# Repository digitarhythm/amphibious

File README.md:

# Amphibious
TReK Amphibious KiCAD Project

[Firmware repository](https://github.com/digitarhythm/vial-qmk/tree/digitarhythm/keyboards/trek/amphibious)

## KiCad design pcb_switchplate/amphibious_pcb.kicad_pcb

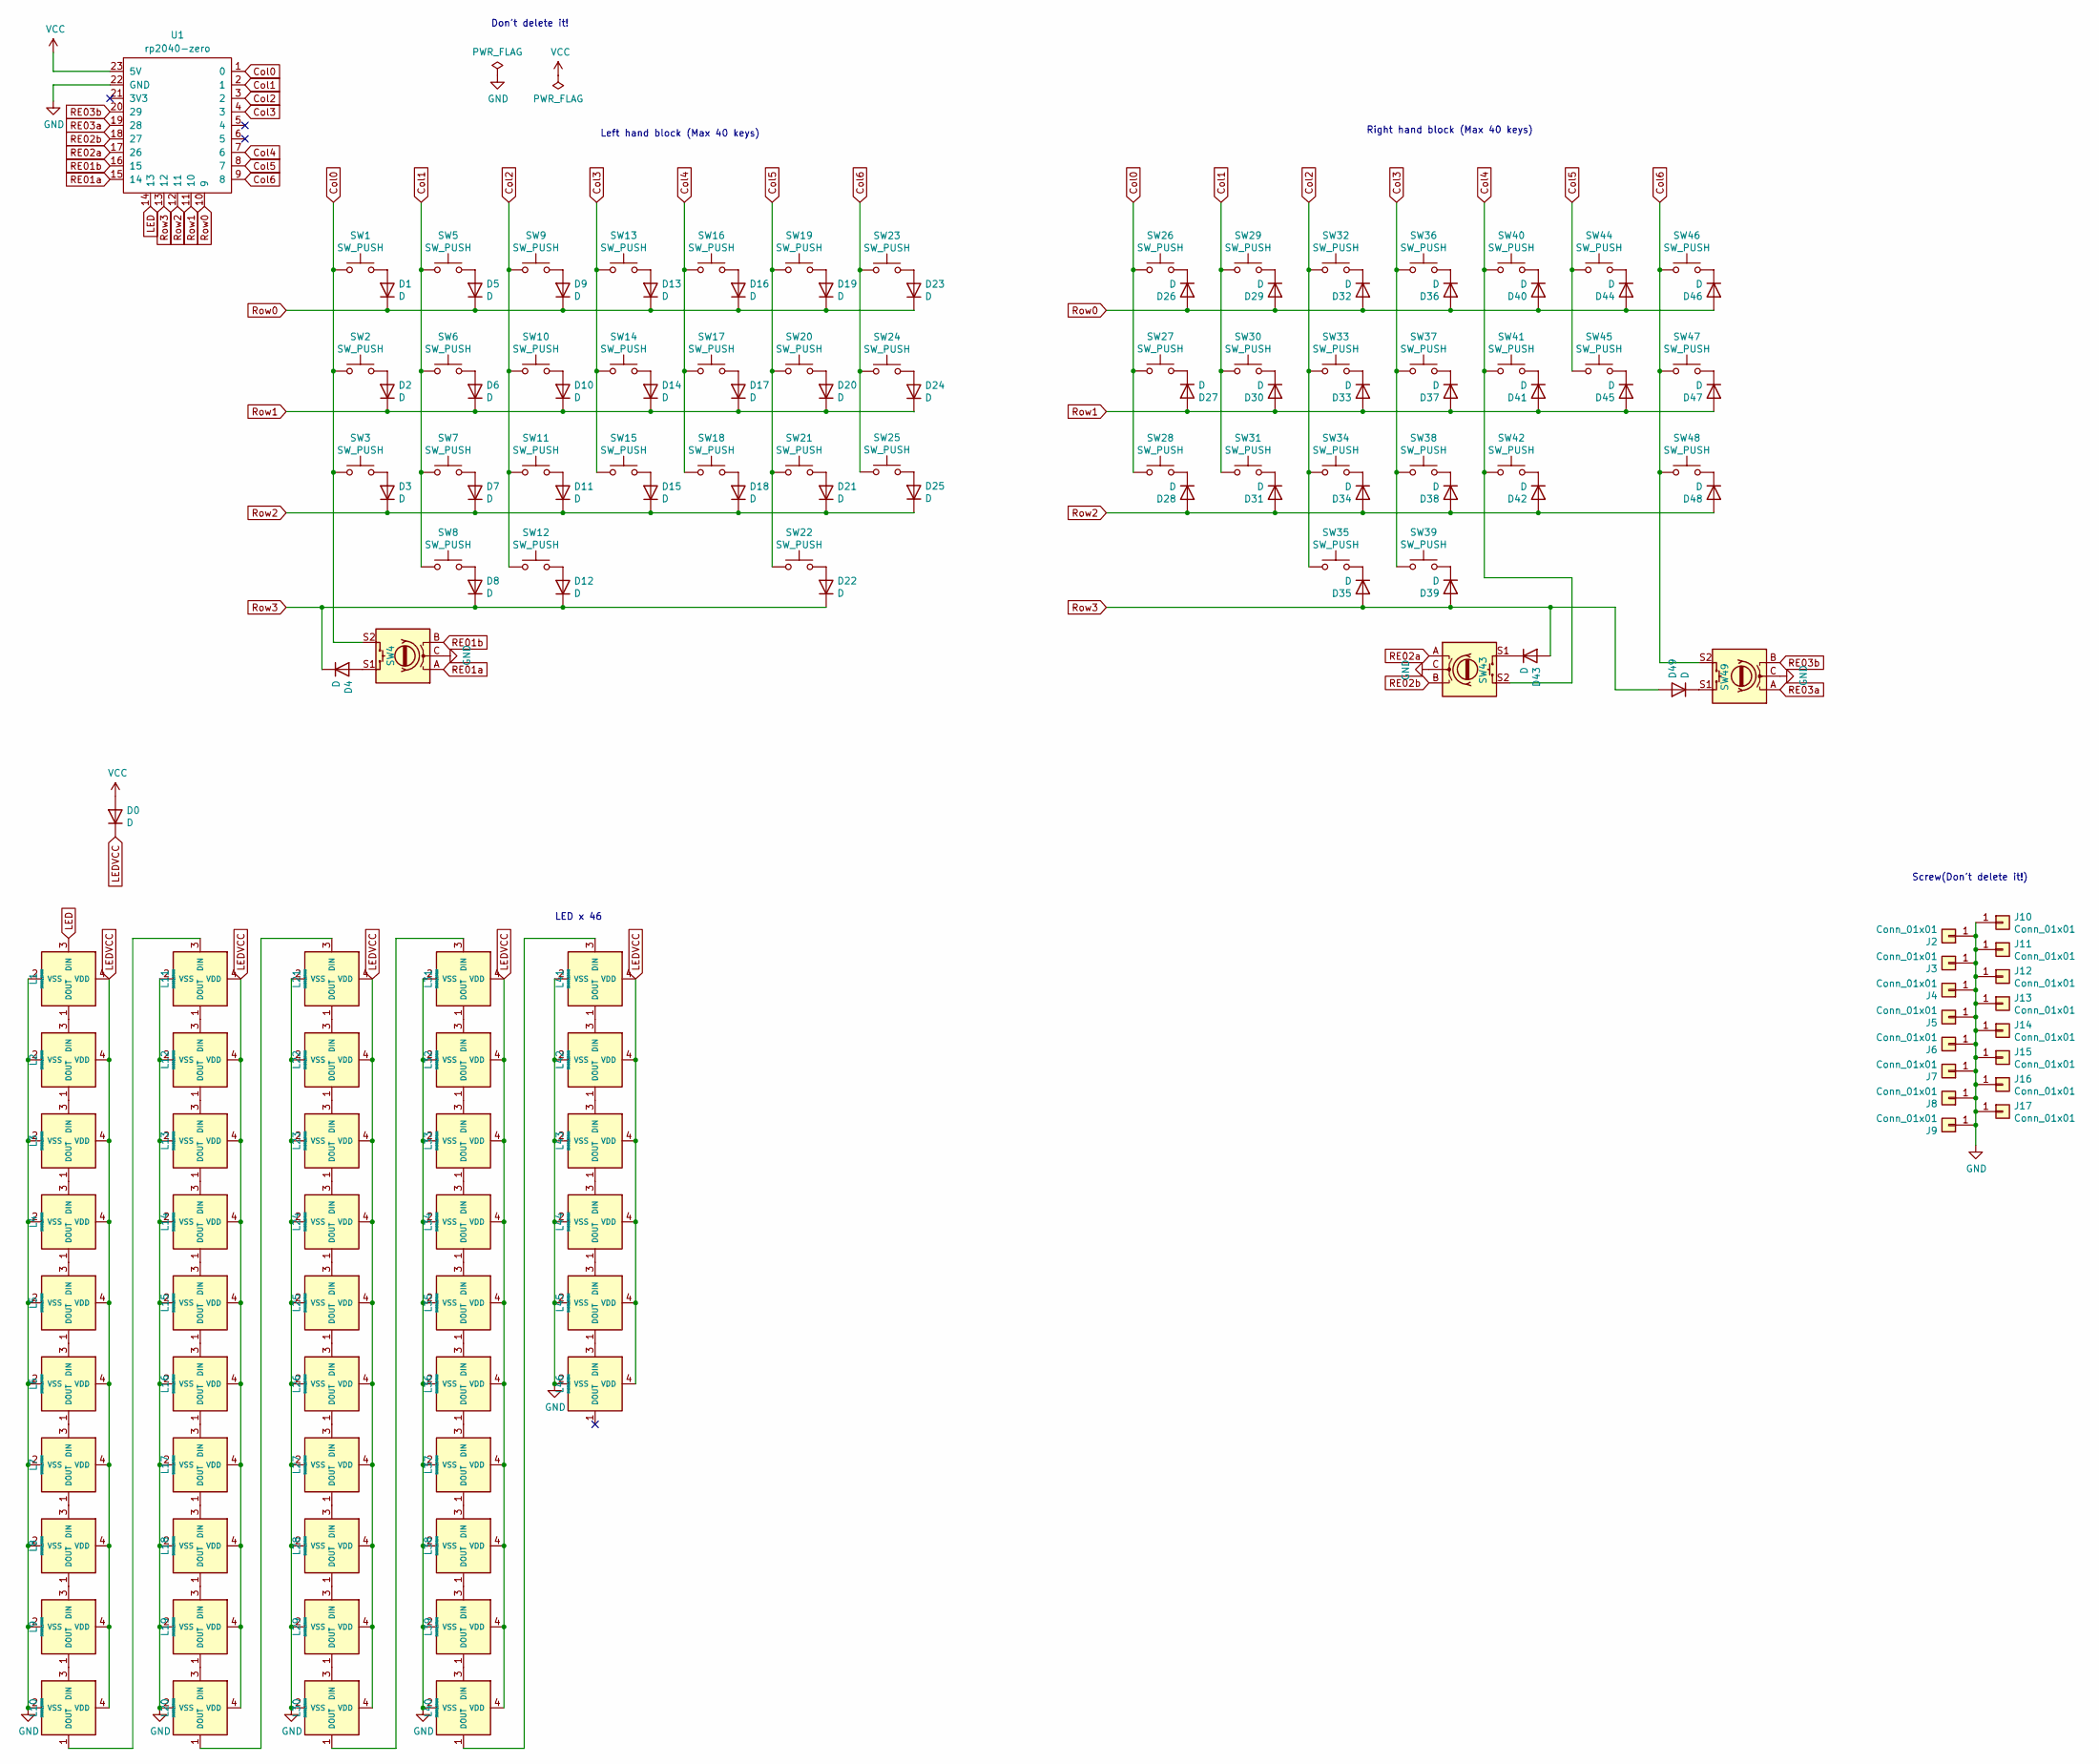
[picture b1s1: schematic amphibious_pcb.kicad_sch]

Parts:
D0, D1, D2, D3, D4, D5, D6, D7, D8, D9, D10, D11, D12, D13, D14, D15, D16, D17, D18, D19, D20, D21, D22, D23, D24, D25, D26, D27, D28, D29, D30, D31, D32, D33, D34, D35, D36, D37, D38, D39, D40, D41, D42, D43, D44, D45, D46, D47, D48, D49: D; Diode_SMD
J2, J3, J4, J5, J6, J7: Conn_01x01; m2_Spacer_Hole_EdgeCuts
J8, J9, J10, J11, J12, J13, J14, J15, J16, J17: Conn_01x01; m2_Screw_Hole_Fab
L1, L2, L3, L4, L5, L6, L7, L8, L9, L10, L11, L12, L13, L14, L15, L16, L17, L18, L19, L20, L21, L22, L23, L24, L25, L26, L27, L28, L29, L30, L31, L32, L33, L34, L35, L36, L37, L38, L39, L40, L41, L42, L43, L44, L45, L46: SK6812MINI; LED_SK6812MINI-E_BL
SW1, SW5, SW6, SW7, SW8, SW9, SW10, SW11, SW13, SW14, SW15, SW16, SW17, SW18, SW19, SW20, SW21, SW23, SW24, SW25, SW26, SW27, SW28, SW29, SW30, SW31, SW32, SW33, SW34, SW36, SW37, SW38, SW40, SW41, SW42, SW44, SW45: SW_PUSH; CherryMX_Hotswap_1u
SW2, SW12, SW35, SW39, SW47: SW_PUSH; CherryMX_Hotswap_1.25u
SW3, SW48: SW_PUSH; CherryMX_Hotswap_1.75u
SW4, SW43, SW49: RotaryEncoder_Switch; SW_Cherry_MX_1.00u_Kailh_EC12
SW22: SW_PUSH; CherryMX_Hotswap_6.25u
SW46: SW_PUSH; CherryMX_Hotswap_1.5u
U1: rp2040-zero; rp2040-zero(pattern only)

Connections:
Col0: SW1.1, SW2.1, SW3.1, SW4.S2, SW26.1, SW27.1, SW28.1, U1.1 (0)
Col1: SW5.1, SW6.1, SW7.1, SW8.1, SW29.1, SW30.1, SW31.1, U1.2 (1)
Col2: SW9.1, SW10.1, SW11.1, SW12.1, SW32.1, SW33.1, SW34.1, SW35.1, U1.3 (2)
Col3: SW13.1, SW14.1, SW15.1, SW36.1, SW37.1, SW38.1, SW39.1, U1.4 (3)
Col4: SW16.1, SW17.1, SW18.1, SW40.1, SW41.1, SW42.1, SW43.S2, U1.7 (6)
Col5: SW19.1, SW20.1, SW21.1, SW22.1, SW44.1, SW45.1, U1.8 (7)
Col6: SW23.1, SW24.1, SW25.1, SW46.1, SW47.1, SW48.1, SW49.S2, U1.9 (8)
GND: J2.1, J3.1, J4.1, J5.1, J6.1, J7.1, J8.1, J9.1, J10.1, J11.1, J12.1, J13.1, J14.1, J15.1, J16.1, J17.1, L1.2 (VSS), L2.2 (VSS), L3.2 (VSS), L4.2 (VSS), L5.2 (VSS), L6.2 (VSS), L7.2 (VSS), L8.2 (VSS), L9.2 (VSS), L10.2 (VSS), L11.2 (VSS), L12.2 (VSS), L13.2 (VSS), L14.2 (VSS), L15.2 (VSS), L16.2 (VSS), L17.2 (VSS), L18.2 (VSS), L19.2 (VSS), L20.2 (VSS), L21.2 (VSS), L22.2 (VSS), L23.2 (VSS), L24.2 (VSS), L25.2 (VSS), L26.2 (VSS), L27.2 (VSS), L28.2 (VSS), L29.2 (VSS), L30.2 (VSS), L31.2 (VSS), L32.2 (VSS), L33.2 (VSS), L34.2 (VSS), L35.2 (VSS), L36.2 (VSS), L37.2 (VSS), L38.2 (VSS), L39.2 (VSS), L40.2 (VSS), L41.2 (VSS), L42.2 (VSS), L43.2 (VSS), L44.2 (VSS), L45.2 (VSS), L46.2 (VSS), SW4.C, SW43.C, SW49.C, U1.22 (GND)
LED: L1.3 (DIN), U1.14 (13)
LEDVCC: D0.1 (K), L1.4 (VDD), L2.4 (VDD), L3.4 (VDD), L4.4 (VDD), L5.4 (VDD), L6.4 (VDD), L7.4 (VDD), L8.4 (VDD), L9.4 (VDD), L10.4 (VDD), L11.4 (VDD), L12.4 (VDD), L13.4 (VDD), L14.4 (VDD), L15.4 (VDD), L16.4 (VDD), L17.4 (VDD), L18.4 (VDD), L19.4 (VDD), L20.4 (VDD), L21.4 (VDD), L22.4 (VDD), L23.4 (VDD), L24.4 (VDD), L25.4 (VDD), L26.4 (VDD), L27.4 (VDD), L28.4 (VDD), L29.4 (VDD), L30.4 (VDD), L31.4 (VDD), L32.4 (VDD), L33.4 (VDD), L34.4 (VDD), L35.4 (VDD), L36.4 (VDD), L37.4 (VDD), L38.4 (VDD), L39.4 (VDD), L40.4 (VDD), L41.4 (VDD), L42.4 (VDD), L43.4 (VDD), L44.4 (VDD), L45.4 (VDD), L46.4 (VDD)
unnamed: D1.2 (A), SW1.2
unnamed: D2.2 (A), SW2.2
unnamed: D3.2 (A), SW3.2
unnamed: D4.2 (A), SW4.S1
unnamed: D5.2 (A), SW5.2
unnamed: D6.2 (A), SW6.2
unnamed: D7.2 (A), SW7.2
unnamed: D8.2 (A), SW8.2
unnamed: D9.2 (A), SW9.2
unnamed: D10.2 (A), SW10.2
unnamed: D11.2 (A), SW11.2
unnamed: D12.2 (A), SW12.2
unnamed: D13.2 (A), SW13.2
unnamed: D14.2 (A), SW14.2
unnamed: D15.2 (A), SW15.2
unnamed: D16.2 (A), SW16.2
unnamed: D17.2 (A), SW17.2
unnamed: D18.2 (A), SW18.2
unnamed: D19.2 (A), SW19.2
unnamed: D20.2 (A), SW20.2
unnamed: D21.2 (A), SW21.2
unnamed: D22.2 (A), SW22.2
unnamed: D23.2 (A), SW23.2
unnamed: D24.2 (A), SW24.2
unnamed: D25.2 (A), SW25.2
unnamed: D26.1 (K), SW26.2
unnamed: D27.1 (K), SW27.2
unnamed: D28.1 (K), SW28.2
unnamed: D29.1 (K), SW29.2
unnamed: D30.1 (K), SW30.2
unnamed: D31.1 (K), SW31.2
unnamed: D32.1 (K), SW32.2
unnamed: D33.1 (K), SW33.2
unnamed: D34.1 (K), SW34.2
unnamed: D35.1 (K), SW35.2
unnamed: D36.1 (K), SW36.2
unnamed: D37.1 (K), SW37.2
unnamed: D38.1 (K), SW38.2
unnamed: D39.1 (K), SW39.2
unnamed: D40.1 (K), SW40.2
unnamed: D41.1 (K), SW41.2
unnamed: D42.1 (K), SW42.2
unnamed: D43.1 (K), SW43.S1
unnamed: D44.1 (K), SW44.2
unnamed: D45.1 (K), SW45.2
unnamed: D46.1 (K), SW46.2
unnamed: D47.1 (K), SW47.2
unnamed: D48.1 (K), SW48.2
unnamed: D49.1 (K), SW49.S1
unnamed: L1.1 (DOUT), L2.3 (DIN)
unnamed: L2.1 (DOUT), L3.3 (DIN)
unnamed: L3.1 (DOUT), L4.3 (DIN)
unnamed: L4.1 (DOUT), L5.3 (DIN)
unnamed: L5.1 (DOUT), L6.3 (DIN)
unnamed: L6.1 (DOUT), L7.3 (DIN)
unnamed: L7.1 (DOUT), L8.3 (DIN)
unnamed: L8.1 (DOUT), L9.3 (DIN)
unnamed: L9.1 (DOUT), L10.3 (DIN)
unnamed: L10.1 (DOUT), L11.3 (DIN)
unnamed: L11.1 (DOUT), L12.3 (DIN)
unnamed: L12.1 (DOUT), L13.3 (DIN)
unnamed: L13.1 (DOUT), L14.3 (DIN)
unnamed: L14.1 (DOUT), L15.3 (DIN)
unnamed: L15.1 (DOUT), L16.3 (DIN)
unnamed: L16.1 (DOUT), L17.3 (DIN)
unnamed: L17.1 (DOUT), L18.3 (DIN)
unnamed: L18.1 (DOUT), L19.3 (DIN)
unnamed: L19.1 (DOUT), L20.3 (DIN)
unnamed: L20.1 (DOUT), L21.3 (DIN)
unnamed: L21.1 (DOUT), L22.3 (DIN)
unnamed: L22.1 (DOUT), L23.3 (DIN)
unnamed: L23.1 (DOUT), L24.3 (DIN)
unnamed: L24.1 (DOUT), L25.3 (DIN)
unnamed: L25.1 (DOUT), L26.3 (DIN)
unnamed: L26.1 (DOUT), L27.3 (DIN)
unnamed: L27.1 (DOUT), L28.3 (DIN)
unnamed: L28.1 (DOUT), L29.3 (DIN)
unnamed: L29.1 (DOUT), L30.3 (DIN)
unnamed: L30.1 (DOUT), L31.3 (DIN)
unnamed: L31.1 (DOUT), L32.3 (DIN)
unnamed: L32.1 (DOUT), L33.3 (DIN)
unnamed: L33.1 (DOUT), L34.3 (DIN)
unnamed: L34.1 (DOUT), L35.3 (DIN)
unnamed: L35.1 (DOUT), L36.3 (DIN)
unnamed: L36.1 (DOUT), L37.3 (DIN)
unnamed: L37.1 (DOUT), L38.3 (DIN)
unnamed: L38.1 (DOUT), L39.3 (DIN)
unnamed: L39.1 (DOUT), L40.3 (DIN)
unnamed: L40.1 (DOUT), L41.3 (DIN)
unnamed: L41.1 (DOUT), L42.3 (DIN)
unnamed: L42.1 (DOUT), L43.3 (DIN)
unnamed: L43.1 (DOUT), L44.3 (DIN)
unnamed: L44.1 (DOUT), L45.3 (DIN)
unnamed: L45.1 (DOUT), L46.3 (DIN)
RE01a: SW4.A, U1.15 (14)
RE01b: SW4.B, U1.16 (15)
RE02a: SW43.A, U1.17 (26)
RE02b: SW43.B, U1.18 (27)
RE03a: SW49.A, U1.19 (28)
RE03b: SW49.B, U1.20 (29)
Row0: D1.1 (K), D5.1 (K), D9.1 (K), D13.1 (K), D16.1 (K), D19.1 (K), D23.1 (K), D26.2 (A), D29.2 (A), D32.2 (A), D36.2 (A), D40.2 (A), D44.2 (A), D46.2 (A), U1.10 (9)
Row1: D2.1 (K), D6.1 (K), D10.1 (K), D14.1 (K), D17.1 (K), D20.1 (K), D24.1 (K), D27.2 (A), D30.2 (A), D33.2 (A), D37.2 (A), D41.2 (A), D45.2 (A), D47.2 (A), U1.11 (10)
Row2: D3.1 (K), D7.1 (K), D11.1 (K), D15.1 (K), D18.1 (K), D21.1 (K), D25.1 (K), D28.2 (A), D31.2 (A), D34.2 (A), D38.2 (A), D42.2 (A), D48.2 (A), U1.12 (11)
Row3: D4.1 (K), D8.1 (K), D12.1 (K), D22.1 (K), D35.2 (A), D39.2 (A), D43.2 (A), D49.2 (A), U1.13 (12)
VCC: D0.2 (A), U1.23 (5V)

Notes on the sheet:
LED x 46
Left hand block (Max 40 keys)
Screw(Don't delete it!)
Don't delete it!
Right hand block (Max 40 keys)

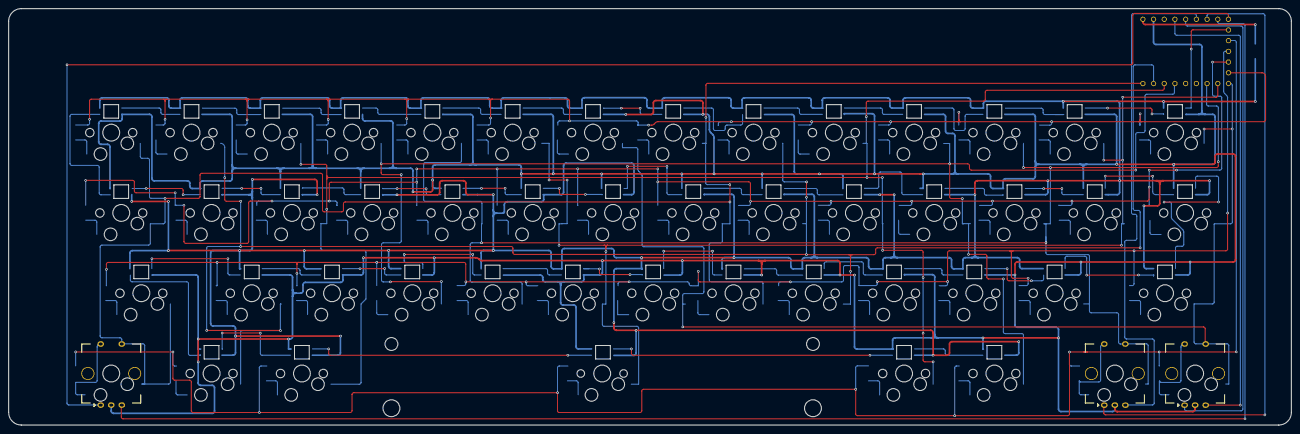
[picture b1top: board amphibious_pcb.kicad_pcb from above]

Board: 2 copper layers, 304.3 x 98.8 mm, 146 parts (0 on the bottom side), 115 nets.

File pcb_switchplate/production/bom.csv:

Designator,Footprint,Quantity,Value,LCSC Part #
"D0, D1, D10, D11, D12, D13, D14, D15, D16, D17, D18, D19, D2, D20, D21, D22, D23, D24, D25, D26, D27, D28, D29, D3, D30, D31, D32, D33, D34, D35, D36, D37, D38, D39, D4, D40, D41, D42, D43, D44, D45, D46, D47, D48, D49, D5, D6, D7, D8, D9",Diode_SMD,50,D,
"L1, L10, L11, L12, L13, L14, L15, L16, L17, L18, L19, L2, L20, L21, L22, L23, L24, L25, L26, L27, L28, L29, L3, L30, L31, L32, L33, L34, L35, L36, L37, L38, L39, L4, L40, L41, L42, L43, L44, L45, L46, L5, L6, L7, L8, L9",LED_SK6812MINI-E_BL,46,SK6812MINI,
"SW1, SW10, SW11, SW13, SW14, SW15, SW16, SW17, SW18, SW19, SW20, SW21, SW23, SW24, SW25, SW26, SW27, SW28, SW29, SW30, SW31, SW32, SW33, SW34, SW36, SW37, SW38, SW39, SW40, SW41, SW42, SW44, SW45, SW5, SW6, SW7, SW8, SW9",CherryMX_Hotswap_1u,38,SW_PUSH,
"SW12, SW2, SW35, SW47",CherryMX_Hotswap_1.25u,4,SW_PUSH,
SW22,CherryMX_Hotswap_6.25u_Rev,1,SW_PUSH,
"SW3, SW48",CherryMX_Hotswap_1.75u,2,SW_PUSH,
"SW4, SW43, SW49",SW_Cherry_MX_1.00u_Kailh_EC12,3,RotaryEncoder_Switch,
SW46,CherryMX_Hotswap_1.5u,1,SW_PUSH,
U1,rp2040-zero(pattern only),1,rp2040-zero,
